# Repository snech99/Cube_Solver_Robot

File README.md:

# Cube_Solver_Robot

This work was created as part of a project in my mechatronics course at Hochschule Wismar, University of Applied Sciences: Technology, Business and Design. 
I worked on it together with a friend of mine. 

It's a Robot which can scan and solve a Rubik's Cube. It's possible to take out the Cube and twitch it by yourself. If you don't want to twist it by yourself, we have a mode which will turn it for you randomly with 20 moves. The Robot have two main modes: **Automatic and external_PC**.
Those modes are explained in a special PDF which you can find in the Repo.

The automatic mode solves the cube using an algorithm we wrote ourselves. It is based on the manual solution method, as a human would solve it.
This Code can be found under the following link: [Repo](https://github.com/snech99/Rubiks_Cube_Solver)

For external communication, the algorithm must be written by the user. There is a Python template for this, which communicates with the robot via a C program.
Download the folder /src/external_PC and compile the C program with make. You can then start the program as follows. You need the sudo privileges to be able to access the USB interface:

```bash
sudo ./main my_script
```

Here are some pictures to get an impression:

| Robot                  | Closeup of the colorsensor               |
| ---------------------- | ---------------------- |
|  |   |

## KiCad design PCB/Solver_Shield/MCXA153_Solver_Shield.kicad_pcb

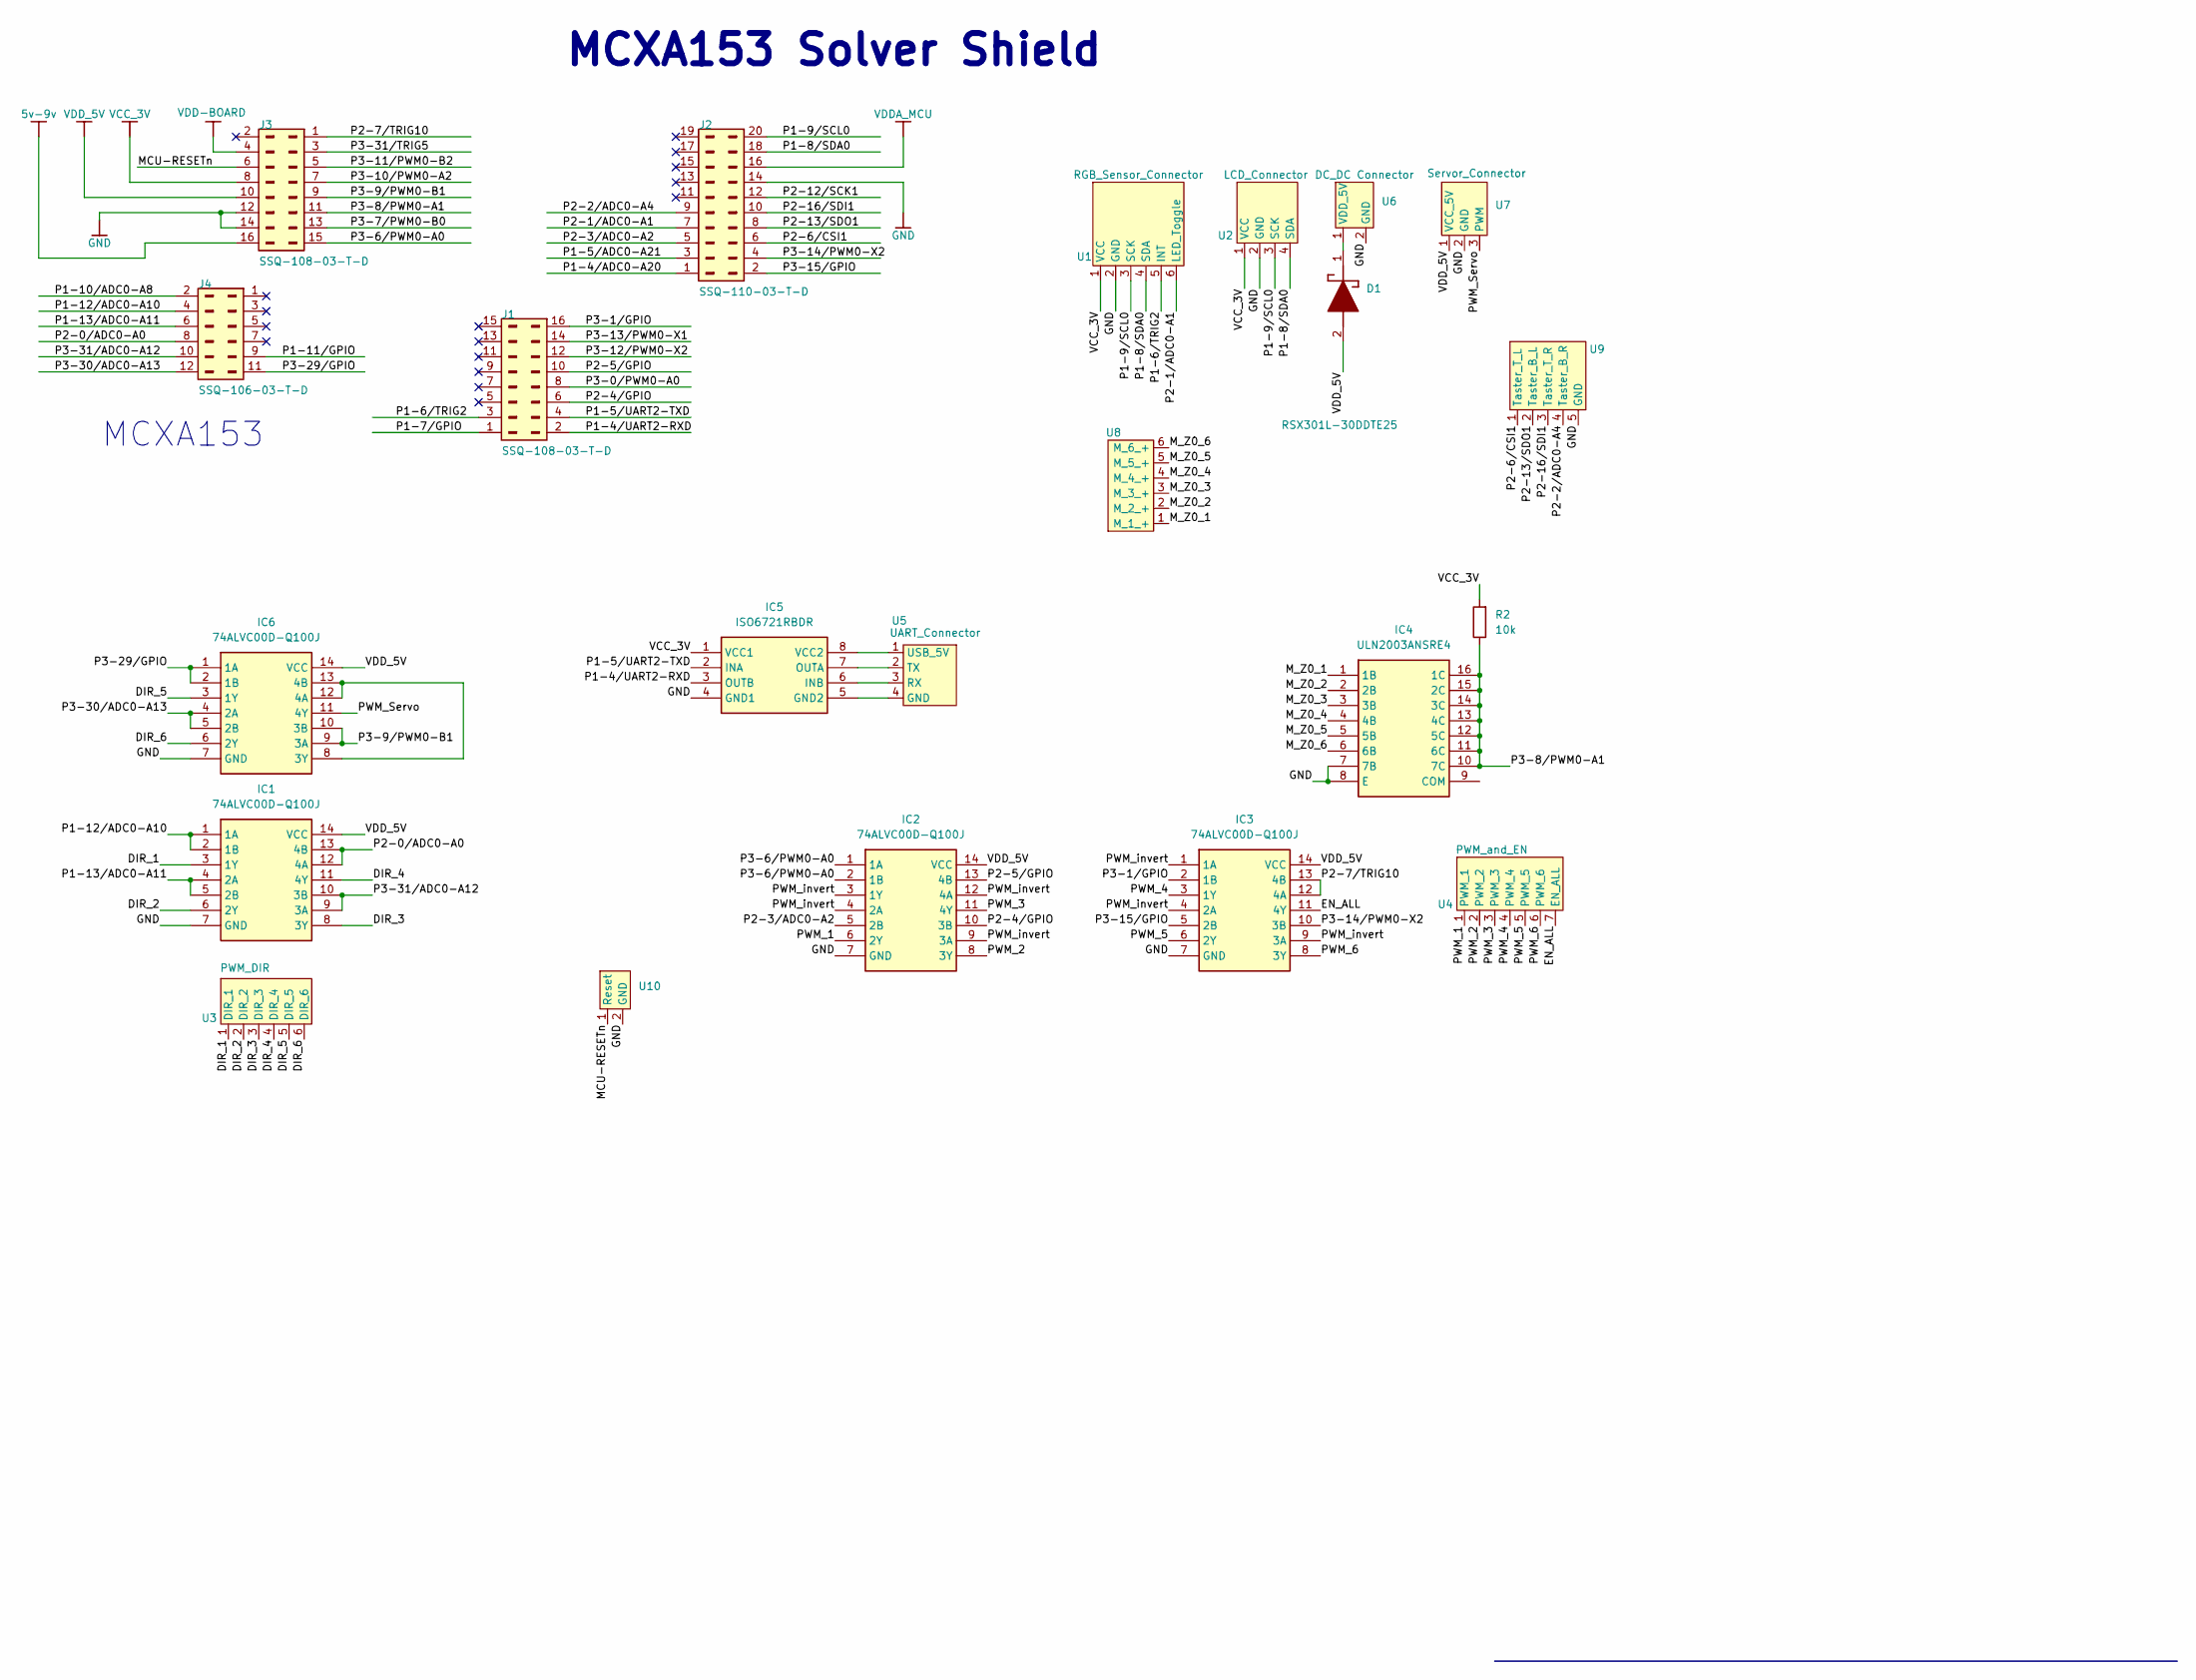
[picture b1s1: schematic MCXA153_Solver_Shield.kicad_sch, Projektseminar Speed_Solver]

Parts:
D1: RSX301L-30DDTE25; DIOM5026X220N; Mouser Part Number 755-RSX301L-30DDTE25
IC1, IC2, IC3, IC6: 74ALVC00D-Q100J; SOIC127P600X175-14N; Mouser Part Number 771-74ALVC00DQ100J
IC4: ULN2003ANSRE4; SOIC127P780X200-16N; Mouser Part Number 595-ULN2003ANSRE4
IC5: ISO6721RBDR; SOIC127P600X175-8N; Mouser Part Number 595-ISO6721RBDR
J1, J3: SSQ-108-03-T-D; MANUFACTURER PART NUMBER SSQ-108-03-T-D
J2: SSQ-110-03-T-D; MANUFACTURER PART NUMBER SSQ-110-03-T-D
J4: SSQ-106-03-T-D; MANUFACTURER PART NUMBER SSQ-106-03-T-D
R2: 10k; R_0603_1608Metric_Pad0.98x0.95mm_HandSolder
U1: Pinheader_Sensor
U2: Pinheader_LCD
U3: PWM_DIR
U4: Treiber_PWM
U5: UART
U6: VDD_5V
U7: Servo
U8: Z0
U9: Taster
U10: Reset_Connector

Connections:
5v-9v: J3.16
/DIR_1: IC1.3 (1Y), U3.1 (DIR)
/DIR_2: IC1.6 (2Y), U3.2 (DIR)
/DIR_3: IC1.8 (3Y), U3.3 (DIR)
/DIR_4: IC1.11 (4Y), U3.4 (DIR)
/DIR_5: IC6.3 (1Y), U3.5 (DIR)
/DIR_6: IC6.6 (2Y), U3.6 (DIR)
/EN_ALL: IC3.11 (4Y), U4.7 (EN_ALL)
/MCU-RESETn: J3.6, U10.1 (Reset)
/M_Z0_1: IC4.1 (1B), U8.1 (M_1_+)
/M_Z0_2: IC4.2 (2B), U8.2 (M_2_+)
/M_Z0_3: IC4.3 (3B), U8.3 (M_3_+)
/M_Z0_4: IC4.4 (4B), U8.4 (M_4_+)
/M_Z0_5: IC4.5 (5B), U8.5 (M_5_+)
/M_Z0_6: IC4.6 (6B), U8.6 (M_6_+)
/P1-4/ADC0-A20: J2.1
/P1-4/UART2-RXD: IC5.3 (OUTB), J1.2
/P1-5/ADC0-A21: J2.3
/P1-5/UART2-TXD: IC5.2 (INA), J1.4
/P1-6/TRIG2: J1.3, U1.5 (INT)
/P1-7/GPIO: J1.1
/P1-8/SDA0: J2.18, U1.4 (SDA), U2.4 (SDA)
/P1-9/SCL0: J2.20, U1.3 (SCK), U2.3 (SCK)
/P1-10/ADC0-A8: J4.2
/P1-11/GPIO: J4.9
/P1-12/ADC0-A10: IC1.1 (1A), IC1.2 (1B), J4.4
/P1-13/ADC0-A11: IC1.4 (2A), IC1.5 (2B), J4.6
/P2-0/ADC0-A0: IC1.12 (4A), IC1.13 (4B), J4.8
/P2-1/ADC0-A1: J2.7, U1.6 (LED_Toggle)
/P2-2/ADC0-A4: J2.9, U9.4 (Taster_B_R)
/P2-3/ADC0-A2: IC2.5 (2B), J2.5
/P2-4/GPIO: IC2.10 (3B), J1.6
/P2-5/GPIO: IC2.13 (4B), J1.10
/P2-6/CSI1: J2.6, U9.1 (Taster_T_L)
/P2-7/TRIG10: IC3.12 (4A), IC3.13 (4B), J3.1
/P2-12/SCK1: J2.12
/P2-13/SDO1: J2.8, U9.2 (Taster_B_L)
/P2-16/SDI1: J2.10, U9.3 (Taster_T_R)
/P3-0/PWM0-A0: J1.8
/P3-1/GPIO: IC3.2 (1B), J1.16
/P3-6/PWM0-A0: IC2.1 (1A), IC2.2 (1B), J3.15
/P3-7/PWM0-B0: J3.13
/P3-8/PWM0-A1: IC4.10 (7C), IC4.11 (6C), IC4.12 (5C), IC4.13 (4C), IC4.14 (3C), IC4.15 (2C), IC4.16 (1C), J3.11, R2.1
/P3-9/PWM0-B1: IC6.9 (3A), IC6.10 (3B), J3.9
/P3-10/PWM0-A2: J3.7
/P3-11/PWM0-B2: J3.5
/P3-12/PWM0-X2: J1.12
/P3-13/PWM0-X1: J1.14
/P3-14/PWM0-X2: IC3.10 (3B), J2.4
/P3-15/GPIO: IC3.5 (2B), J2.2
/P3-29/GPIO: IC6.1 (1A), IC6.2 (1B), J4.11
/P3-30/ADC0-A13: IC6.4 (2A), IC6.5 (2B), J4.12
/P3-31/ADC0-A12: IC1.9 (3A), IC1.10 (3B), J4.10
/P3-31/TRIG5: J3.3
/PWM_1: IC2.6 (2Y), U4.1 (PWM_1)
/PWM_2: IC2.8 (3Y), U4.2 (PWM_2)
/PWM_3: IC2.11 (4Y), U4.3 (PWM_3)
/PWM_4: IC3.3 (1Y), U4.4 (PWM_4)
/PWM_5: IC3.6 (2Y), U4.5 (PWM_5)
/PWM_6: IC3.8 (3Y), U4.6 (PWM_6)
/PWM_Servo: IC6.11 (4Y), U7.3 (PWM)
/PWM_invert: IC2.3 (1Y), IC2.4 (2A), IC2.9 (3A), IC2.12 (4A), IC3.1 (1A), IC3.4 (2A), IC3.9 (3A)
GND: IC1.7 (GND), IC2.7 (GND), IC3.7 (GND), IC4.7 (7B), IC4.8 (E), IC5.4 (GND1), IC6.7 (GND), J2.14, J3.12, J3.14, U1.2 (GND), U2.2 (GND), U6.2 (GND), U7.2 (GND), U9.5 (GND), U10.2 (GND)
unnamed: D1.1 (K), U6.1 (VDD_5V)
unnamed: IC5.5 (GND2), U5.4 (GND)
unnamed: IC5.6 (INB), U5.3 (RX)
unnamed: IC5.7 (OUTA), U5.2 (TX)
unnamed: IC5.8 (VCC2), U5.1 (USB_5V)
unnamed: IC6.8 (3Y), IC6.12 (4A), IC6.13 (4B)
VCC_3V: IC5.1 (VCC1), J3.8, R2.2, U1.1 (VCC), U2.1 (VCC)
VDD-BOARD: J3.4
VDDA_MCU: J2.16
VDD_5V: D1.2 (A), IC1.14 (VCC), IC2.14 (VCC), IC3.14 (VCC), IC6.14 (VCC), J3.10, U7.1 (VCC_5V)

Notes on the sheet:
MCXA153 Solver Shield
MCXA153

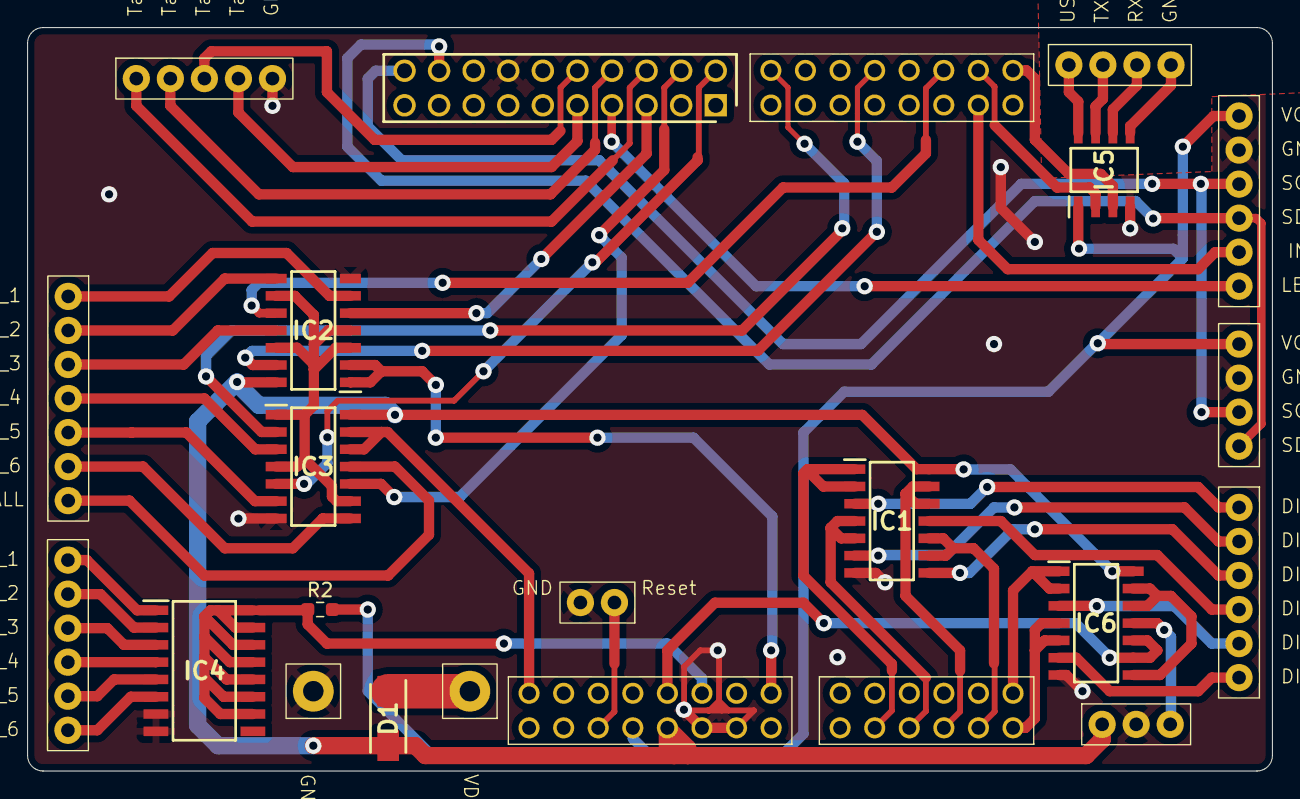
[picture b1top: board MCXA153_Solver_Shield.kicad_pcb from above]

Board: 2 copper layers, 91.4 x 54.6 mm, 22 parts (0 on the bottom side), 57 nets.

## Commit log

2024-11-29 first big push
2024-11-29 add State_Machine_PIC
2024-12-11 New PCB and cool Stuff
2024-12-12 config befor LCD
2024-12-12 a lot in Mue Code
2024-12-13 Last befor Christmas
2025-01-07 COM Done
2025-01-07 a lot muC
2025-01-08 Adding Boxenstop and Bugfixes in Solver
2025-01-08 Adding Cube_Change to extern_PC
2025-01-08 Scan without Servo-Movement
2025-01-09 Add Handshake
2025-01-09 Add Handshake on muC and faster Scan
2025-01-10 Change Language
2025-01-10 Update LICENSE
2025-01-10 Adding PNG
2025-01-11 small Bugfix and adding manual
2025-01-12 Documentation
2025-01-13 small changes and Doku
2025-01-13 change
2025-01-13 Last from muC
2025-02-06 add double-moves and upgrade config
2025-02-12 changes for Sensor
2025-02-12 changing .gitignore
2025-02-12 adding 3D Model
2025-02-12 update Manuel
2025-02-12 update PCB
2025-02-13 small change in main
2025-02-13 change in double move
2025-04-05 update for Steinbrecher-Code
2025-04-05 adding comments and pics
2025-04-05 small change
2025-04-05 pic try
2025-04-05 pics
2025-04-05 update Manual
